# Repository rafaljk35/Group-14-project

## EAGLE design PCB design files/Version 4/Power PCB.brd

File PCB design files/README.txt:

Folder for storing PCB design and schematics

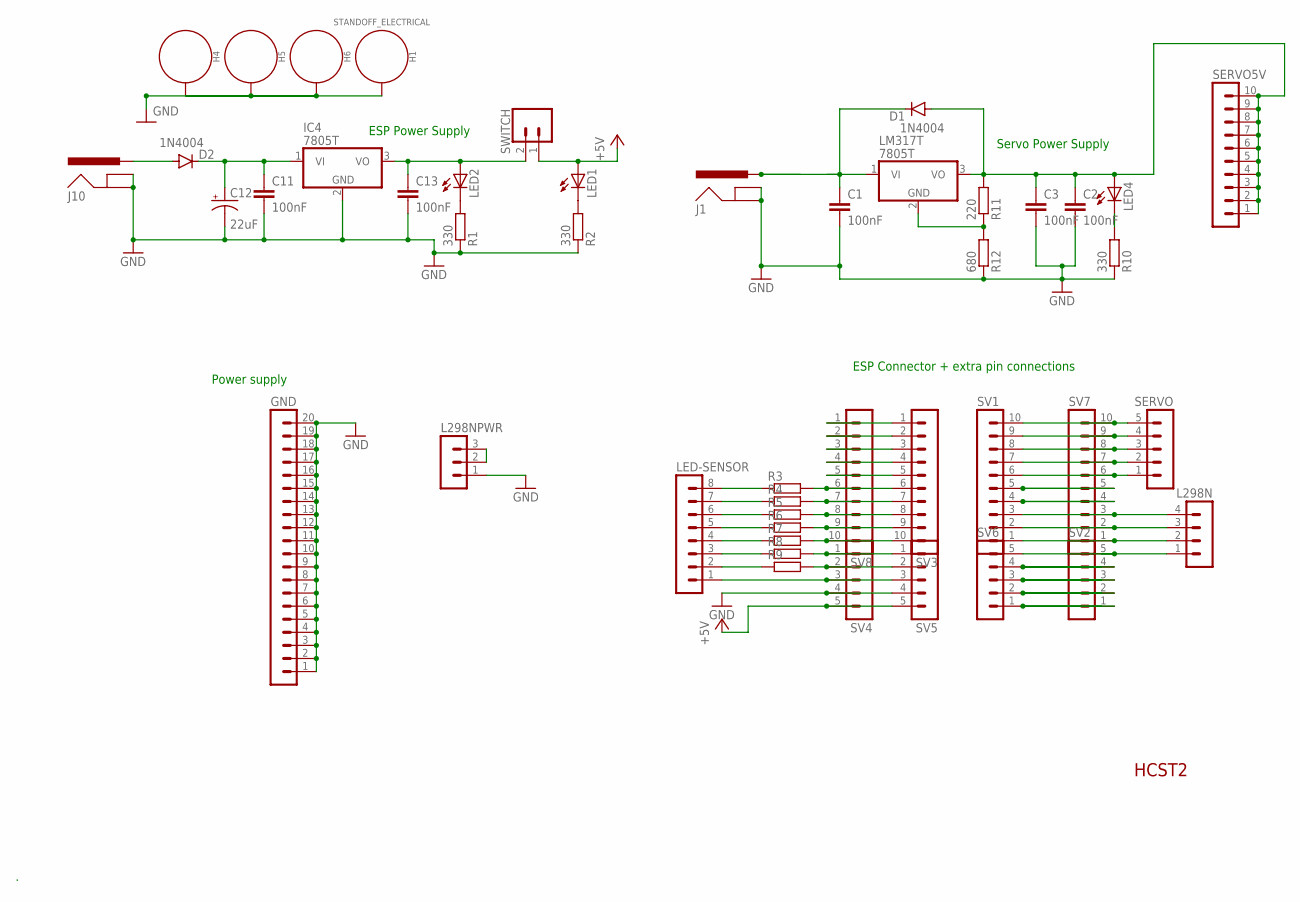
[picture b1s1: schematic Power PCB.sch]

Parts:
C1, C2, C3, C11, C13: 100nF; C2.5-2
C12: 22uF; E2,5-7
D1, D2: 1N4004; DO41-10
GND: MA20-1
H1, H4, H5, H6: STANDOFF_ELECTRICAL; STANDOFF-ELECTRICAL
IC4: 7805T; TO220H
J1, J10: EL311-ROBOT_SPARKFUN-CONNECTORS_POWER_JACKPTH; EL311-ROBOT_SPARKFUN-CONNECTORS_POWER_JACK_PTH
L298N: MA04-1
L298NPWR: MA03-1
LED1, LED2, LED4: LED3MM
LED-SENSOR: MA08-1
LM317T: 7805T; TO220H
R1, R2, R10: 330; 0207/10
R3, R4, R5, R6, R7, R8, R9: R-EU_0207/10; 0207/10
R11: 220; 0207/10
R12: 680; 0207/10
SERVO: MA05-1
SERVO5V: MA10-1
SV1, SV3, SV7, SV8: MA10-1
SV2, SV4, SV5, SV6: MA05-1
SWITCH: CONN_02; 1X02

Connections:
+5V: LED1.A, SV4.5, SV5.5, SWITCH.1
GND: C1.2, C2.2, C3.2, C11.2, C12.-, C13.2, GND.1, GND.2, GND.3, GND.4, GND.5, GND.6, GND.7, GND.8, GND.9, GND.10, GND.11, GND.12, GND.13, GND.14, GND.15, GND.16, GND.17, GND.18, GND.19, GND.20, H1.P1, H4.P1, H5.P1, H6.P1, IC4.2 (GND), J1.GND, J1.GNDBREAK, J10.GND, J10.GNDBREAK, L298NPWR.1, R1.1, R2.1, R10.1, R12.1, SV4.4, SV5.4
unnamed: L298N.1, SV2.5, SV6.5
unnamed: SV1.5, SV7.5
unnamed: SV1.4, SV7.4
unnamed: SV2.4, SV6.4
unnamed: SV2.3, SV6.3
unnamed: LM317T.2 (GND), R11.1, R12.2
unnamed: L298N.2, SV1.1, SV7.1
unnamed: L298N.3, SV1.2, SV7.2
unnamed: L298N.4, SV1.3, SV7.3
unnamed: SERVO.4, SV1.9, SV7.9
unnamed: SERVO.3, SV1.8, SV7.8
unnamed: SERVO.2, SV1.7, SV7.7
unnamed: SERVO.1, SV1.6, SV7.6
unnamed: SV2.2, SV6.2
unnamed: C2.1, C3.1, D1.A, LED4.A, LM317T.3 (VO), R11.2, SERVO5V.1, SERVO5V.2, SERVO5V.3, SERVO5V.4, SERVO5V.5, SERVO5V.6, SERVO5V.7, SERVO5V.8, SERVO5V.9, SERVO5V.10
unnamed: LED-SENSOR.2, R9.1
unnamed: LED4.K (C), R10.2
unnamed: SV2.1, SV6.1
unnamed: SV3.1, SV8.1
unnamed: SV3.2, SV8.2
unnamed: SV3.3, SV8.3
unnamed: LED-SENSOR.1, SV4.3, SV5.3
unnamed: R9.2, SV4.2, SV5.2
unnamed: R8.2, SV4.1, SV5.1
unnamed: R7.2, SV3.10, SV8.10
unnamed: R6.2, SV3.9, SV8.9
unnamed: R5.2, SV3.8, SV8.8
unnamed: R4.2, SV3.7, SV8.7
unnamed: SV3.4, SV8.4
unnamed: SV3.5, SV8.5
unnamed: R3.2, SV3.6, SV8.6
unnamed: C13.1, IC4.3 (VO), LED2.A, SWITCH.2
unnamed: L298NPWR.2, L298NPWR.3
unnamed: LED2.K (C), R1.2
unnamed: LED1.K (C), R2.2
unnamed: LED-SENSOR.8, R3.1
unnamed: LED-SENSOR.7, R4.1
unnamed: LED-SENSOR.6, R5.1
unnamed: LED-SENSOR.5, R6.1
unnamed: LED-SENSOR.4, R7.1
unnamed: LED-SENSOR.3, R8.1
unnamed: SERVO.5, SV1.10, SV7.10
PWR1: C1.1, D1.C, J1.PWR, LM317T.1 (VI)
PWR3: D2.A, J10.PWR
PWR4: C11.1, C12.+, D2.C, IC4.1 (VI)

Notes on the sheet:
HCST2
ESP Power Supply
ESP Connector + extra pin connections
Power supply
Servo Power Supply

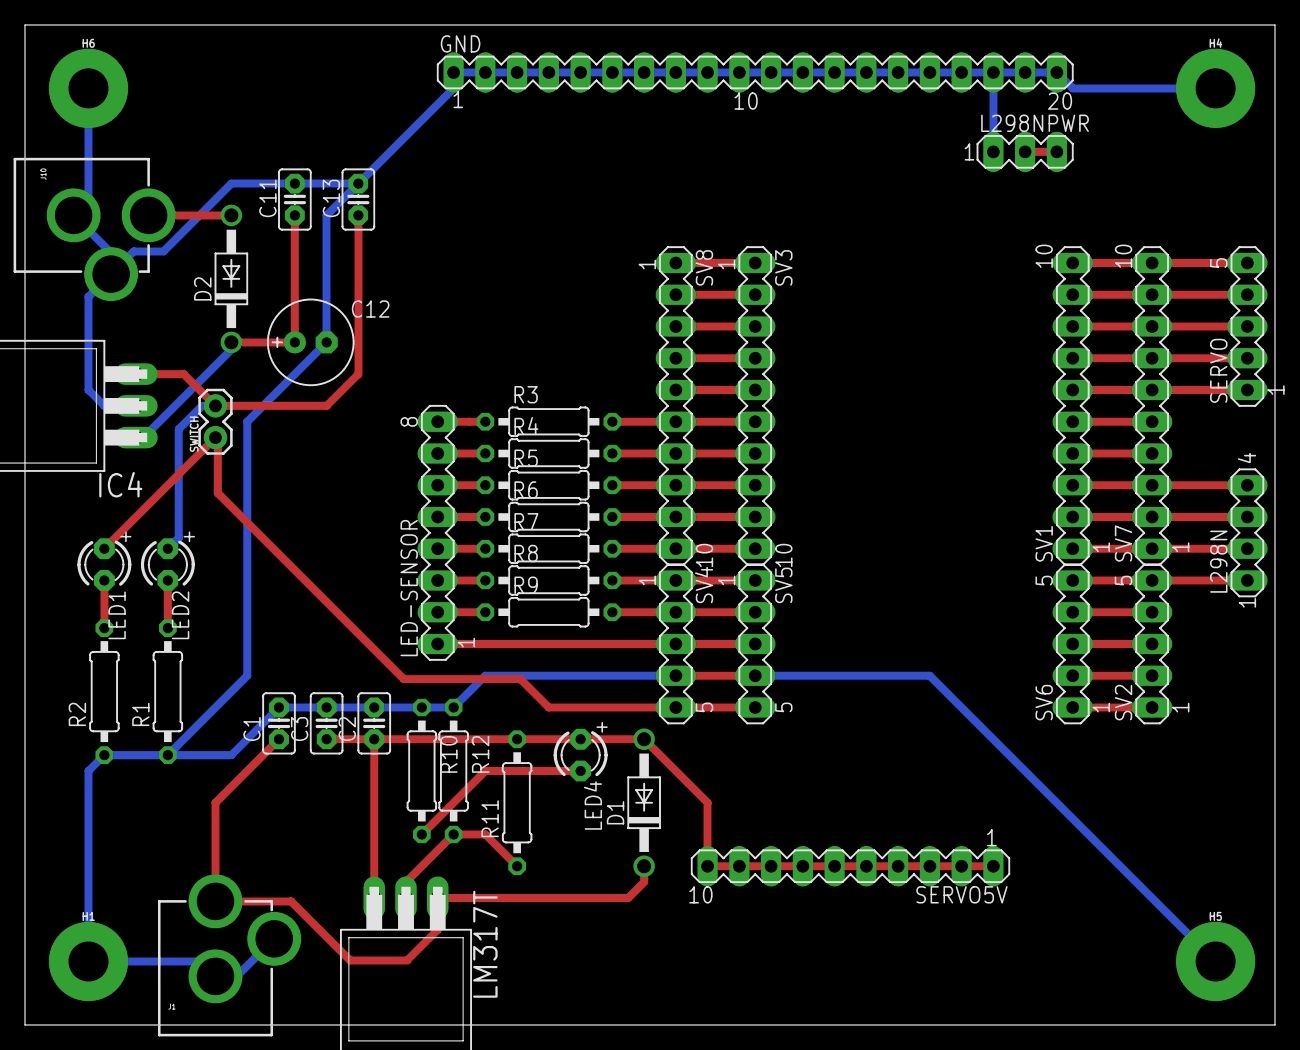
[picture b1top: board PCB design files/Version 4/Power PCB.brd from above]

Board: 2 copper layers, 100.0 x 80.0 mm, 46 parts (0 on the bottom side), 47 nets.

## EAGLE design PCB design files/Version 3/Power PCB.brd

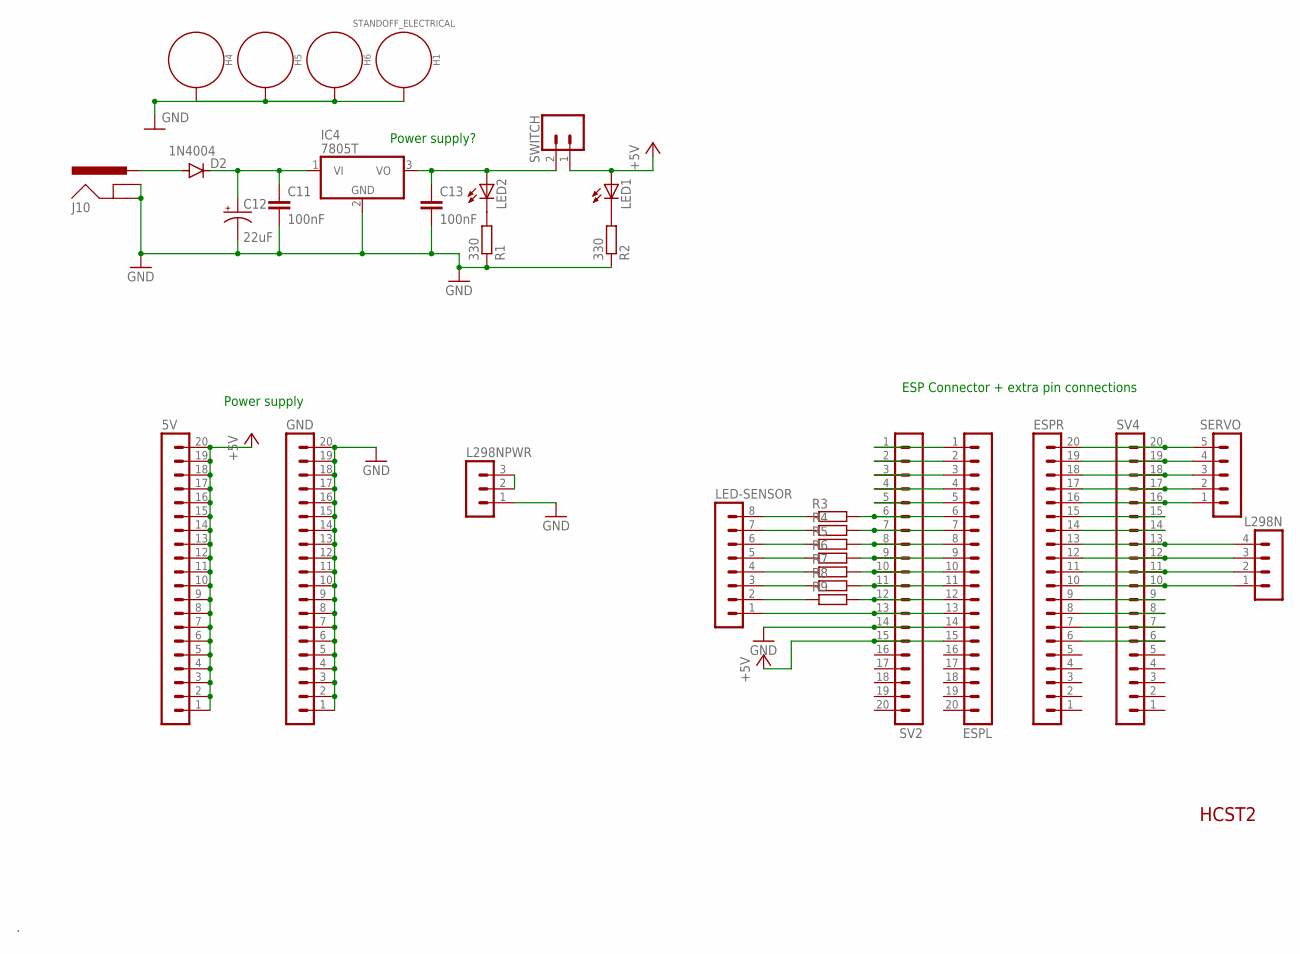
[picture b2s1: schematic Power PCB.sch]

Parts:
5V: MA20-1
C11, C13: 100nF; C2.5-2
C12: 22uF; E2,5-7
D2: 1N4004; DO41-10
ESPL: MA20-1
ESPR: MA20-1
GND: MA20-1
H1, H4, H5, H6: STANDOFF_ELECTRICAL; STANDOFF-ELECTRICAL
IC4: 7805T; TO220H
J10: EL311-ROBOT_SPARKFUN-CONNECTORS_POWER_JACKPTH; EL311-ROBOT_SPARKFUN-CONNECTORS_POWER_JACK_PTH
L298N: MA04-1
L298NPWR: MA03-1
LED1, LED2: LED3MM
LED-SENSOR: MA08-1
R1, R2: 330; 0207/10
R3, R4, R5, R6, R7, R8, R9: R-EU_0207/10; 0207/10
SERVO: MA05-1
SV2, SV4: MA20-1
SWITCH: CONN_02; 1X02

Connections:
+5V: 5V.1, 5V.2, 5V.3, 5V.4, 5V.5, 5V.6, 5V.7, 5V.8, 5V.9, 5V.10, 5V.11, 5V.12, 5V.13, 5V.14, 5V.15, 5V.16, 5V.17, 5V.18, 5V.19, 5V.20, ESPL.15, LED1.A, SV2.15, SWITCH.1
GND: C11.2, C12.-, C13.2, ESPL.14, GND.1, GND.2, GND.3, GND.4, GND.5, GND.6, GND.7, GND.8, GND.9, GND.10, GND.11, GND.12, GND.13, GND.14, GND.15, GND.16, GND.17, GND.18, GND.19, GND.20, H1.P1, H4.P1, H5.P1, H6.P1, IC4.2 (GND), J10.GND, J10.GNDBREAK, L298NPWR.1, R1.1, R2.1, SV2.14
unnamed: ESPR.10, L298N.1, SV4.10
unnamed: ESPR.9, SV4.9
unnamed: ESPR.8, SV4.8
unnamed: ESPR.7, SV4.7
unnamed: ESPR.6, SV4.6
unnamed: ESPR.11, L298N.2, SV4.11
unnamed: ESPR.12, L298N.3, SV4.12
unnamed: ESPR.13, L298N.4, SV4.13
unnamed: ESPR.19, SERVO.4, SV4.19
unnamed: ESPR.18, SERVO.3, SV4.18
unnamed: ESPR.17, SERVO.2, SV4.17
unnamed: ESPR.16, SERVO.1, SV4.16
unnamed: ESPR.15, SV4.15
unnamed: LED-SENSOR.2, R9.1
unnamed: ESPR.14, SV4.14
unnamed: ESPL.13, LED-SENSOR.1, SV2.13
unnamed: ESPL.12, R9.2, SV2.12
unnamed: ESPL.11, R8.2, SV2.11
unnamed: ESPL.10, R7.2, SV2.10
unnamed: ESPL.9, R6.2, SV2.9
unnamed: ESPL.8, R5.2, SV2.8
unnamed: ESPL.7, R4.2, SV2.7
unnamed: ESPL.1, SV2.1
unnamed: ESPL.2, SV2.2
unnamed: ESPL.3, SV2.3
unnamed: ESPL.4, SV2.4
unnamed: ESPL.5, SV2.5
unnamed: ESPL.6, R3.2, SV2.6
unnamed: C13.1, IC4.3 (VO), LED2.A, SWITCH.2
unnamed: L298NPWR.2, L298NPWR.3
unnamed: LED2.K (C), R1.2
unnamed: LED1.K (C), R2.2
unnamed: LED-SENSOR.8, R3.1
unnamed: LED-SENSOR.7, R4.1
unnamed: LED-SENSOR.6, R5.1
unnamed: LED-SENSOR.5, R6.1
unnamed: LED-SENSOR.4, R7.1
unnamed: LED-SENSOR.3, R8.1
unnamed: ESPR.20, SERVO.5, SV4.20
PWR3: D2.A, J10.PWR
PWR4: C11.1, C12.+, D2.C, IC4.1 (VI)

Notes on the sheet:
HCST2
Power supply?
ESP Connector + extra pin connections
Power supply

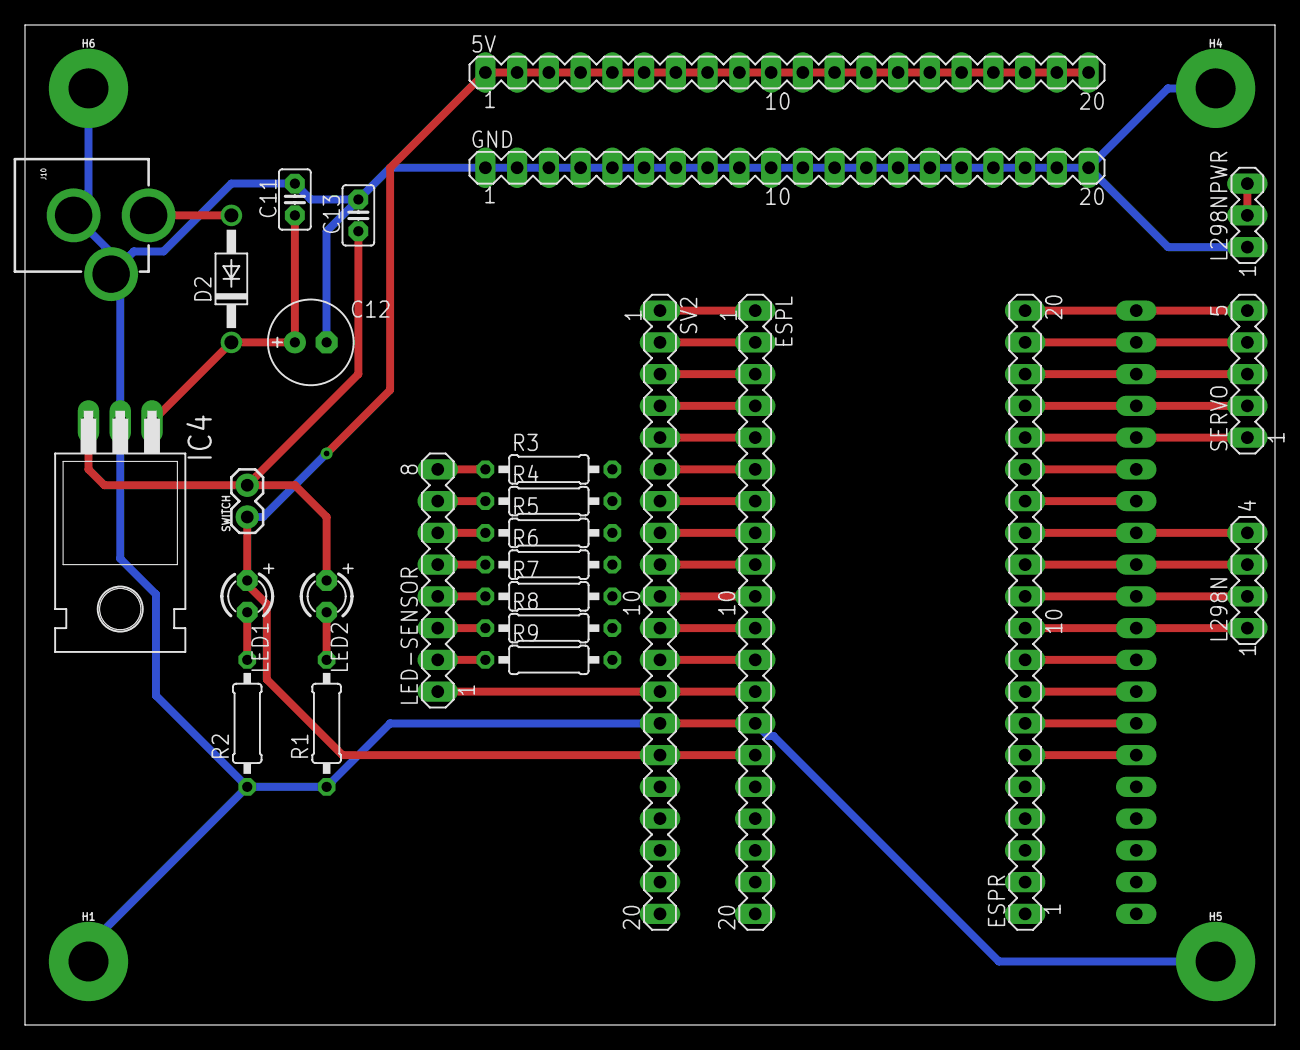
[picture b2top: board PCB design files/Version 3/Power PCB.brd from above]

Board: 2 copper layers, 100.0 x 80.0 mm, 32 parts (1 on the bottom side), 43 nets.

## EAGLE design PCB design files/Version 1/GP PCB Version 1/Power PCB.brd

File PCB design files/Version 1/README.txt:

Version 1 of PCb design. Last modified 2022/12/07

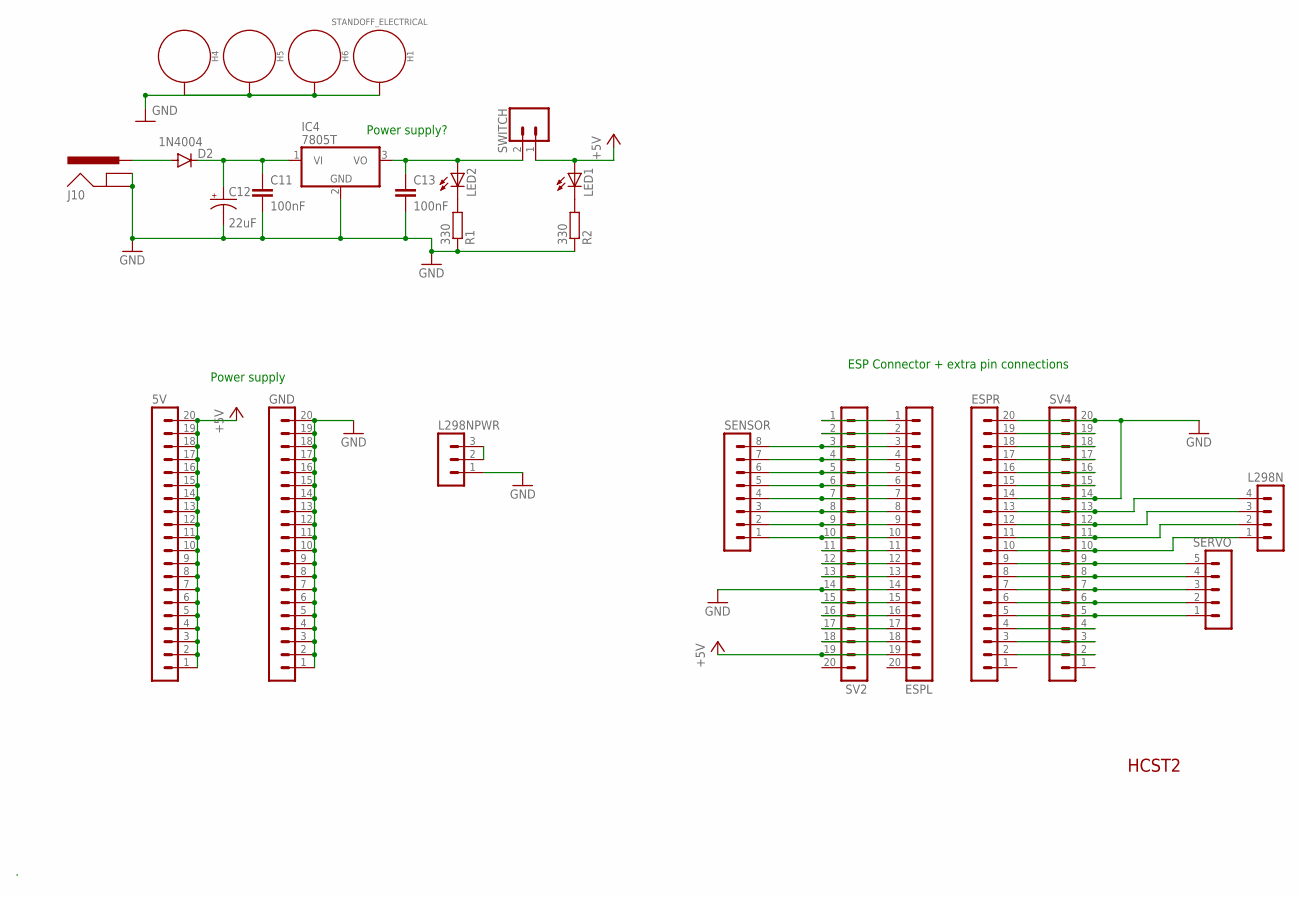
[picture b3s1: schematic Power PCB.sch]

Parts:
5V: MA20-1
C11, C13: 100nF; C2.5-2
C12: 22uF; E2,5-7
D2: 1N4004; DO41-10
ESPL: MA20-1
ESPR: MA20-1
GND: MA20-1
H1, H4, H5, H6: STANDOFF_ELECTRICAL; STANDOFF-ELECTRICAL
IC4: 7805T; TO220H
J10: EL311-ROBOT_SPARKFUN-CONNECTORS_POWER_JACKPTH; EL311-ROBOT_SPARKFUN-CONNECTORS_POWER_JACK_PTH
L298N: MA04-1
L298NPWR: MA03-1
LED1, LED2: LED3MM
R1, R2: 330; 0207/10
SENSOR: MA08-1
SERVO: MA05-1
SV2, SV4: MA20-1
SWITCH: CONN_02; 1X02

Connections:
+5V: 5V.1, 5V.2, 5V.3, 5V.4, 5V.5, 5V.6, 5V.7, 5V.8, 5V.9, 5V.10, 5V.11, 5V.12, 5V.13, 5V.14, 5V.15, 5V.16, 5V.17, 5V.18, 5V.19, 5V.20, ESPL.19, LED1.A, SV2.19, SWITCH.1
GND: C11.2, C12.-, C13.2, ESPL.14, ESPR.14, ESPR.20, GND.1, GND.2, GND.3, GND.4, GND.5, GND.6, GND.7, GND.8, GND.9, GND.10, GND.11, GND.12, GND.13, GND.14, GND.15, GND.16, GND.17, GND.18, GND.19, GND.20, H1.P1, H4.P1, H5.P1, H6.P1, IC4.2 (GND), J10.GND, J10.GNDBREAK, L298NPWR.1, R1.1, R2.1, SV2.14, SV4.14, SV4.20
unnamed: ESPR.10, L298N.1, SV4.10
unnamed: ESPR.9, SERVO.5, SV4.9
unnamed: ESPR.8, SERVO.4, SV4.8
unnamed: ESPR.7, SERVO.3, SV4.7
unnamed: ESPR.6, SERVO.2, SV4.6
unnamed: ESPR.5, SERVO.1, SV4.5
unnamed: ESPR.11, L298N.2, SV4.11
unnamed: ESPR.12, L298N.3, SV4.12
unnamed: ESPR.13, L298N.4, SV4.13
unnamed: ESPR.19, SV4.19
unnamed: ESPR.18, SV4.18
unnamed: ESPR.17, SV4.17
unnamed: ESPR.16, SV4.16
unnamed: ESPR.15, SV4.15
unnamed: ESPR.4, SV4.4
unnamed: ESPR.3, SV4.3
unnamed: ESPR.2, SV4.2
unnamed: ESPL.18, SV2.18
unnamed: ESPL.17, SV2.17
unnamed: ESPL.16, SV2.16
unnamed: ESPL.15, SV2.15
unnamed: ESPL.13, SV2.13
unnamed: ESPL.12, SV2.12
unnamed: ESPL.11, SV2.11
unnamed: ESPL.10, SENSOR.1, SV2.10
unnamed: ESPL.9, SENSOR.2, SV2.9
unnamed: ESPL.8, SENSOR.3, SV2.8
unnamed: ESPL.7, SENSOR.4, SV2.7
unnamed: ESPL.1, SV2.1
unnamed: ESPL.2, SV2.2
unnamed: ESPL.3, SENSOR.8, SV2.3
unnamed: ESPL.4, SENSOR.7, SV2.4
unnamed: ESPL.5, SENSOR.6, SV2.5
unnamed: ESPL.6, SENSOR.5, SV2.6
unnamed: C13.1, IC4.3 (VO), LED2.A, SWITCH.2
unnamed: L298NPWR.2, L298NPWR.3
unnamed: LED2.K (C), R1.2
unnamed: LED1.K (C), R2.2
PWR3: D2.A, J10.PWR
PWR4: C11.1, C12.+, D2.C, IC4.1 (VI)

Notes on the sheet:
HCST2
Power supply?
ESP Connector + extra pin connections
Power supply

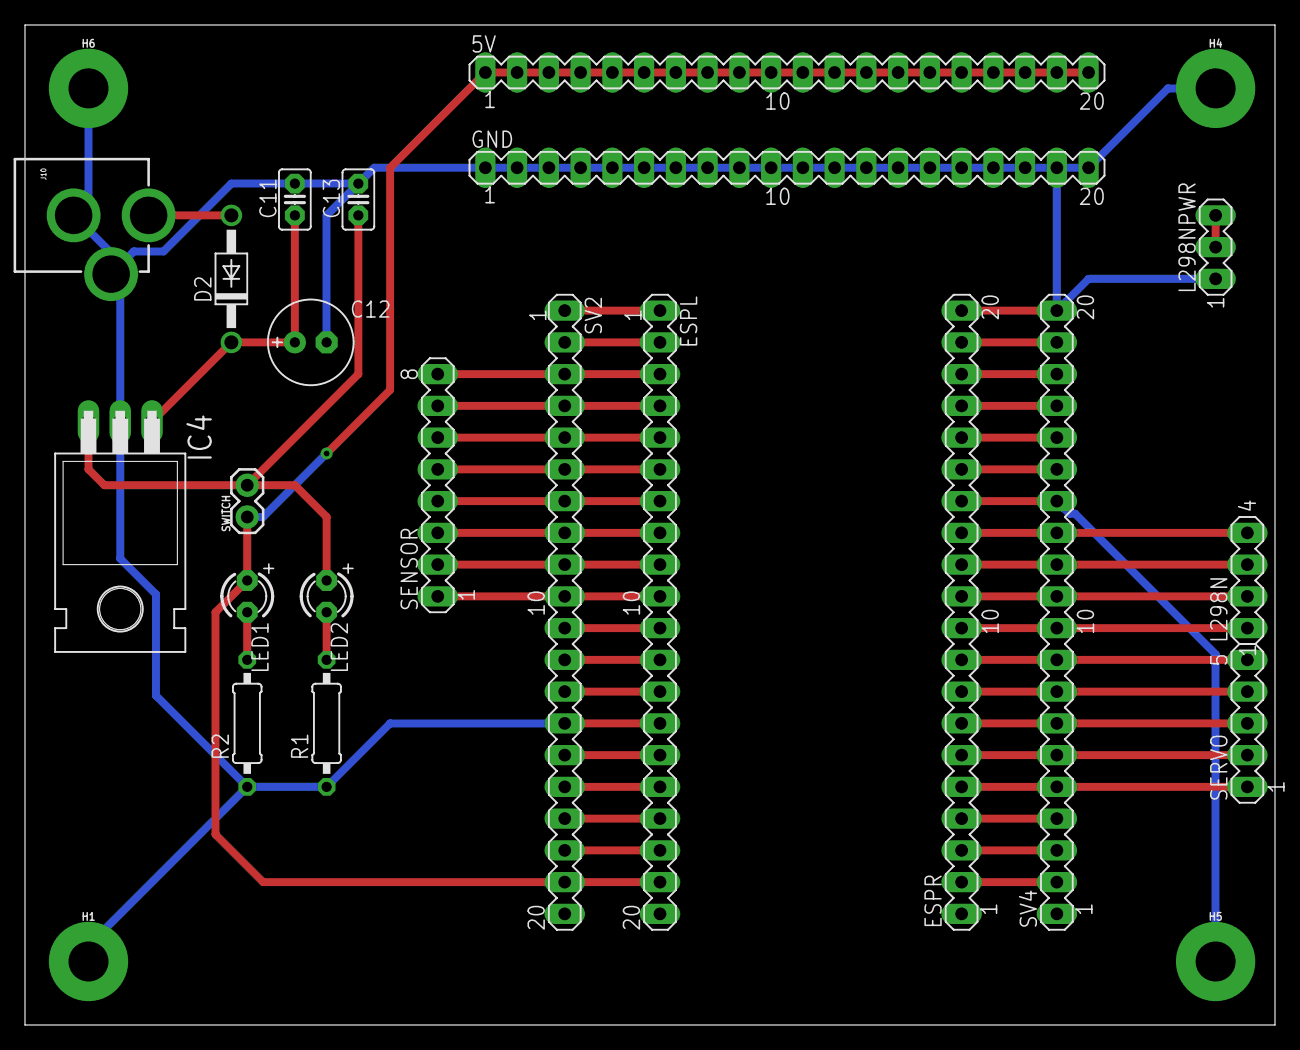
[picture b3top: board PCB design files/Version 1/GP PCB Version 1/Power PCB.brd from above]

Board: 2 copper layers, 100.0 x 80.0 mm, 25 parts (0 on the bottom side), 42 nets.

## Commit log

2022-10-17 Create design files fusion 360
2022-10-19 Update design files fusion 360
2022-10-23 Text file for microcontroller info
    Used for storing information on potential microcontrollers we can use in our project.
2022-10-23 The extra t makes me upset :(
2022-10-23 Datasheet & schematic for mbed
    Uploaded full datasheet for LPC1768, as well as full circuit schematic to build an mbed development board.
2022-10-23 Update Microcontroller info
2022-10-23 Update Microcontroller info
    added date to info
2022-10-23 Added info for ESP32
2022-10-23 Trying to add a folder
2022-10-24 Create folder for esp32 datasheets
2023-01-26 Update esp coding tutorials.txt
    added link for esp we borrowed from the shed
2023-01-30 Create Updated models
2023-01-31 Create folder for PCB design
2023-01-31 PCB version 2
2023-02-08 updated servo control library
    previous link only worked for arduinos not esp
2023-02-09 Version 3 PCB
    Updated PCB design for ESP32 Devkit1
2023-02-13 test code upload
2023-02-20 Added servo lib doc
    Also moved some stuff that is no longer used
2023-02-23 Servo control example
    Example code for controlling 2 servos, including instructions for installing the library and documentation
2023-03-01 PCB design V4
    Added new voltage regulator, fixed ESP connector width
2023-03-17 Added robot column control code
    MADE FOR ARDUINO MEGA, CHANGE SERVO LIBRARY FOR FUNCTION ON ESP32.
    Allows the robot arm to move to the 7 columns of the connect 4 board. Currently only supports column 7, more will be added soon.
2023-03-19 Create Sending
2023-03-25 Add files via upload
    This a the app program use to choose the row. Need to try in lab
2023-03-29 Add files via upload
    setup for Making an app. The png for the icon of the ap.
2023-03-29 new version of robot code
2023-03-29 Random AI code
2023-03-30 Add v2 code
2023-03-31 add functional led detection code

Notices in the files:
parts and their libraries:
SparkFun-Hardware: Licensing: Creative Commons ShareAlike 4.0 International - https://creativecommons.org/licenses/by-sa/4.0
